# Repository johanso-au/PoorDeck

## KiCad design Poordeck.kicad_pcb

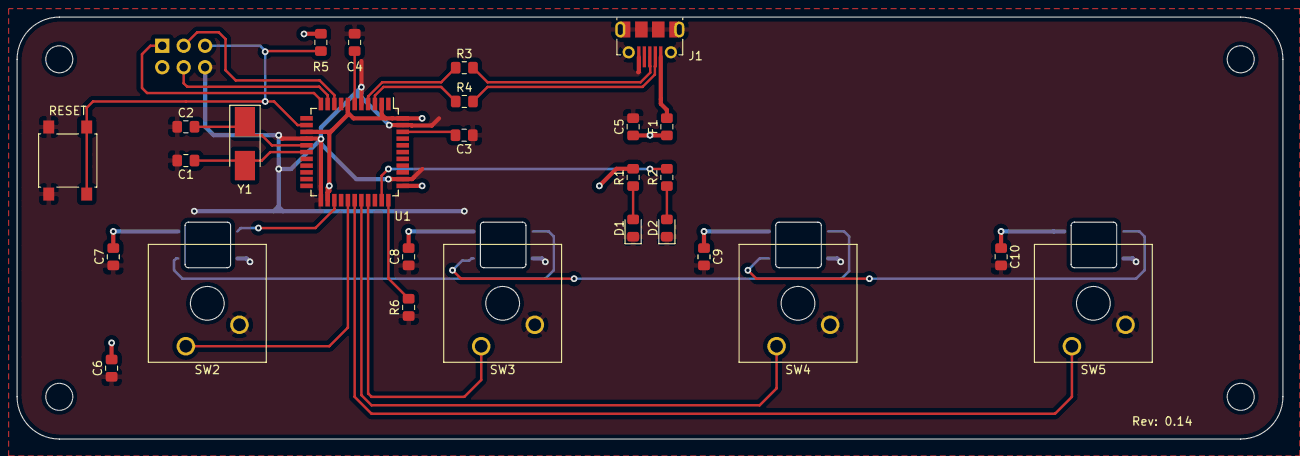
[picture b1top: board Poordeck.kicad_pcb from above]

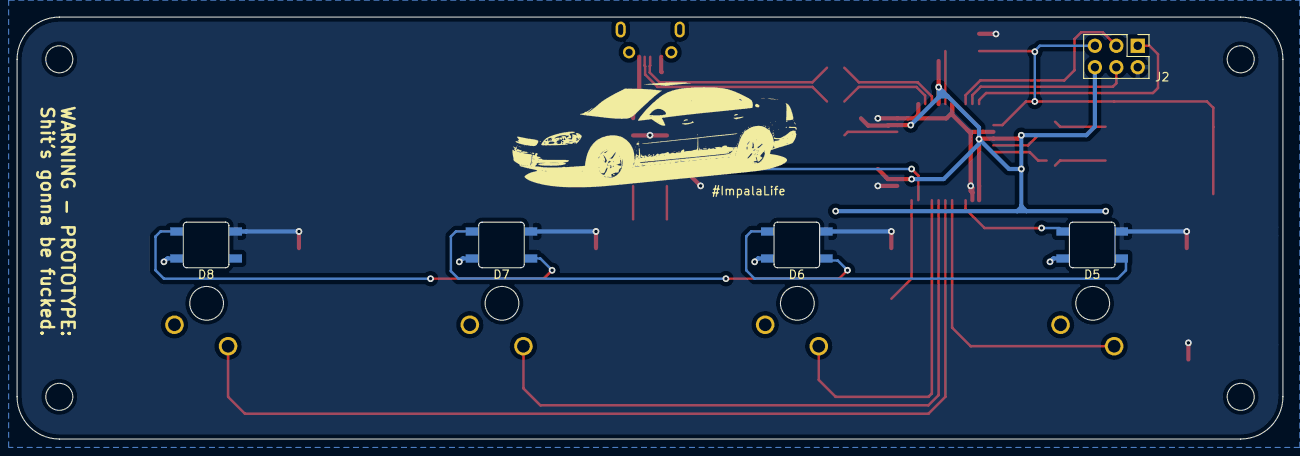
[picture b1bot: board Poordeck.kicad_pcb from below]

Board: 2 copper layers, 150.0 x 50.0 mm, 32 parts (5 on the bottom side), 27 nets.

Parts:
C1, C2: 22pF; C_0805_2012Metric_Pad1.15x1.40mm_HandSolder
C3, C5, C6, C7, C8, C9, C10: 100nF; C_0805_2012Metric_Pad1.15x1.40mm_HandSolder
C4: 1uF; C_0805_2012Metric_Pad1.15x1.40mm_HandSolder
D1, D2: LED; D_0805_2012Metric_Pad1.15x1.40mm_HandSolder
D5, D6, D7, D8: WS2812B; LED_WS2812B_PLCC4_5.0x5.0mm_P3.2mm
F1: 500mA; Fuse_0805_2012Metric_Pad1.15x1.40mm_HandSolder
J1: Molex-105017; USB_Micro-B_Molex-105017-0001
J2: Conn_02x03; PinHeader_2x03_P2.54mm_Vertical
R1, R2, R5, R6: 10k; R_0805_2012Metric_Pad1.15x1.40mm_HandSolder
R3, R4: 22R; R_0805_2012Metric_Pad1.15x1.40mm_HandSolder
RESET: SW_Push; SW_SPST_B3S-1000
SW2, SW3, SW4, SW5: SW_Push; SW_Cherry_MX_1.00u_Plate
U1: ATmega32U4-AU; TQFP-44_10x10mm_P0.8mm
Y1: 16Mhz; Crystal_SMD_5032-2Pin_5.0x3.2mm_HandSoldering

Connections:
+5V: C5.1, C6.1, C7.1, C8.1, C9.1, C10.1, D5.1, D6.1, D7.1, D8.1, F1.1, J2.2, R1.2, R5.1, U1.2, U1.7, U1.14, U1.24, U1.34, U1.44
/AREF: C3.2, U1.42
/HWB: R6.2, U1.33
/XTAL1: C1.1, U1.17, Y1.2
/XTAL2: C2.2, U1.16, Y1.1
/d+: J1.3, R3.2
/d-: J1.2, R4.2
D4: D5.4, U1.25
D6: SW2.1, U1.27
D8: SW5.1, U1.28
D9: SW4.1, U1.29
D10: SW3.1, U1.30
D13: R2.2, U1.32
D+: R3.1, U1.4
D-: R4.1, U1.3
GND: C1.2, C2.1, C3.1, C4.1, C5.2, C6.2, C7.2, C8.2, C9.2, C10.2, D1.1, D2.1, D5.3, D6.3, D7.3, D8.3, J1.5, J1.6, J2.6, R6.1, RESET.1, SW2.2, SW3.2, SW4.2, SW5.2, U1.5, U1.15, U1.23, U1.35, U1.43
MISO: J2.1, U1.11
MOSI: J2.4, U1.10
unnamed: C4.2, U1.6
unnamed: D1.2, R1.1
unnamed: D2.2, R2.1
unnamed: D5.2, D6.4
unnamed: D6.2, D7.4
unnamed: D7.2, D8.4
unnamed: F1.2, J1.1
RESET: J2.5, R5.2, RESET.2, U1.13
SCLK: J2.3, U1.9

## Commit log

2020-06-05 Master Update
